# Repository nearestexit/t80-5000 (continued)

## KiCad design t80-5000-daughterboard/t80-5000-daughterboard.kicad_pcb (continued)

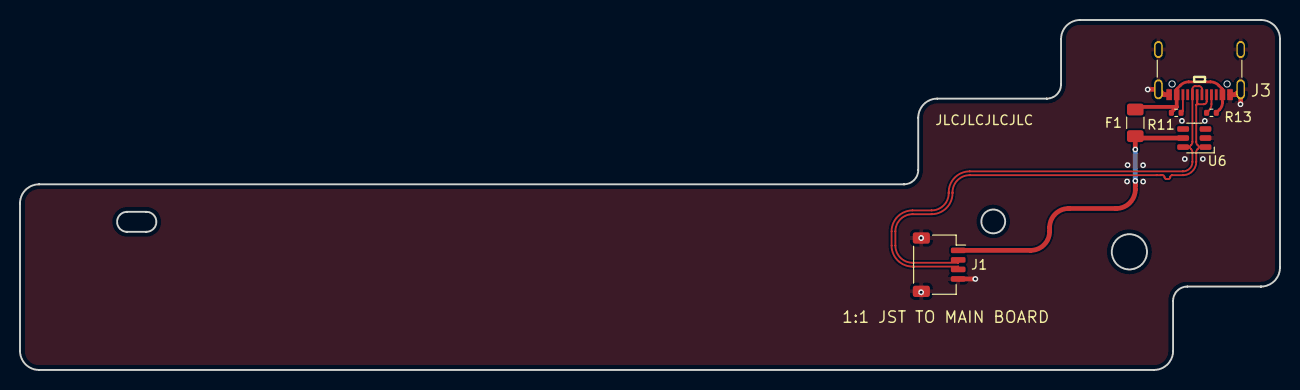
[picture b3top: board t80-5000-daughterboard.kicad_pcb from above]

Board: 2 copper layers, 132.3 x 36.8 mm, 6 parts (0 on the bottom side), 7 nets.

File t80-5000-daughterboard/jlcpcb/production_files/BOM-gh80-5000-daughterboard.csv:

Comment,Designator,Footprint,LCSC,Quantity
56k,"R11,R13",R_0402_1005Metric,C114756,2
Conn_01x04,J1,JST_SH_SM04B-SRSS-TB_1x04-1MP_P1.00mm_Horizontal,C371571,1
USB_C_Receptacle_USB2.0_16P,J3,USB-C-SMD_HANBO_MC-121-L119,C6332278,1
500mA,F1,Fuse_1206_3216Metric,C70076,1
SRV05-4,U6,SOT-23-6-routable,C85364,1

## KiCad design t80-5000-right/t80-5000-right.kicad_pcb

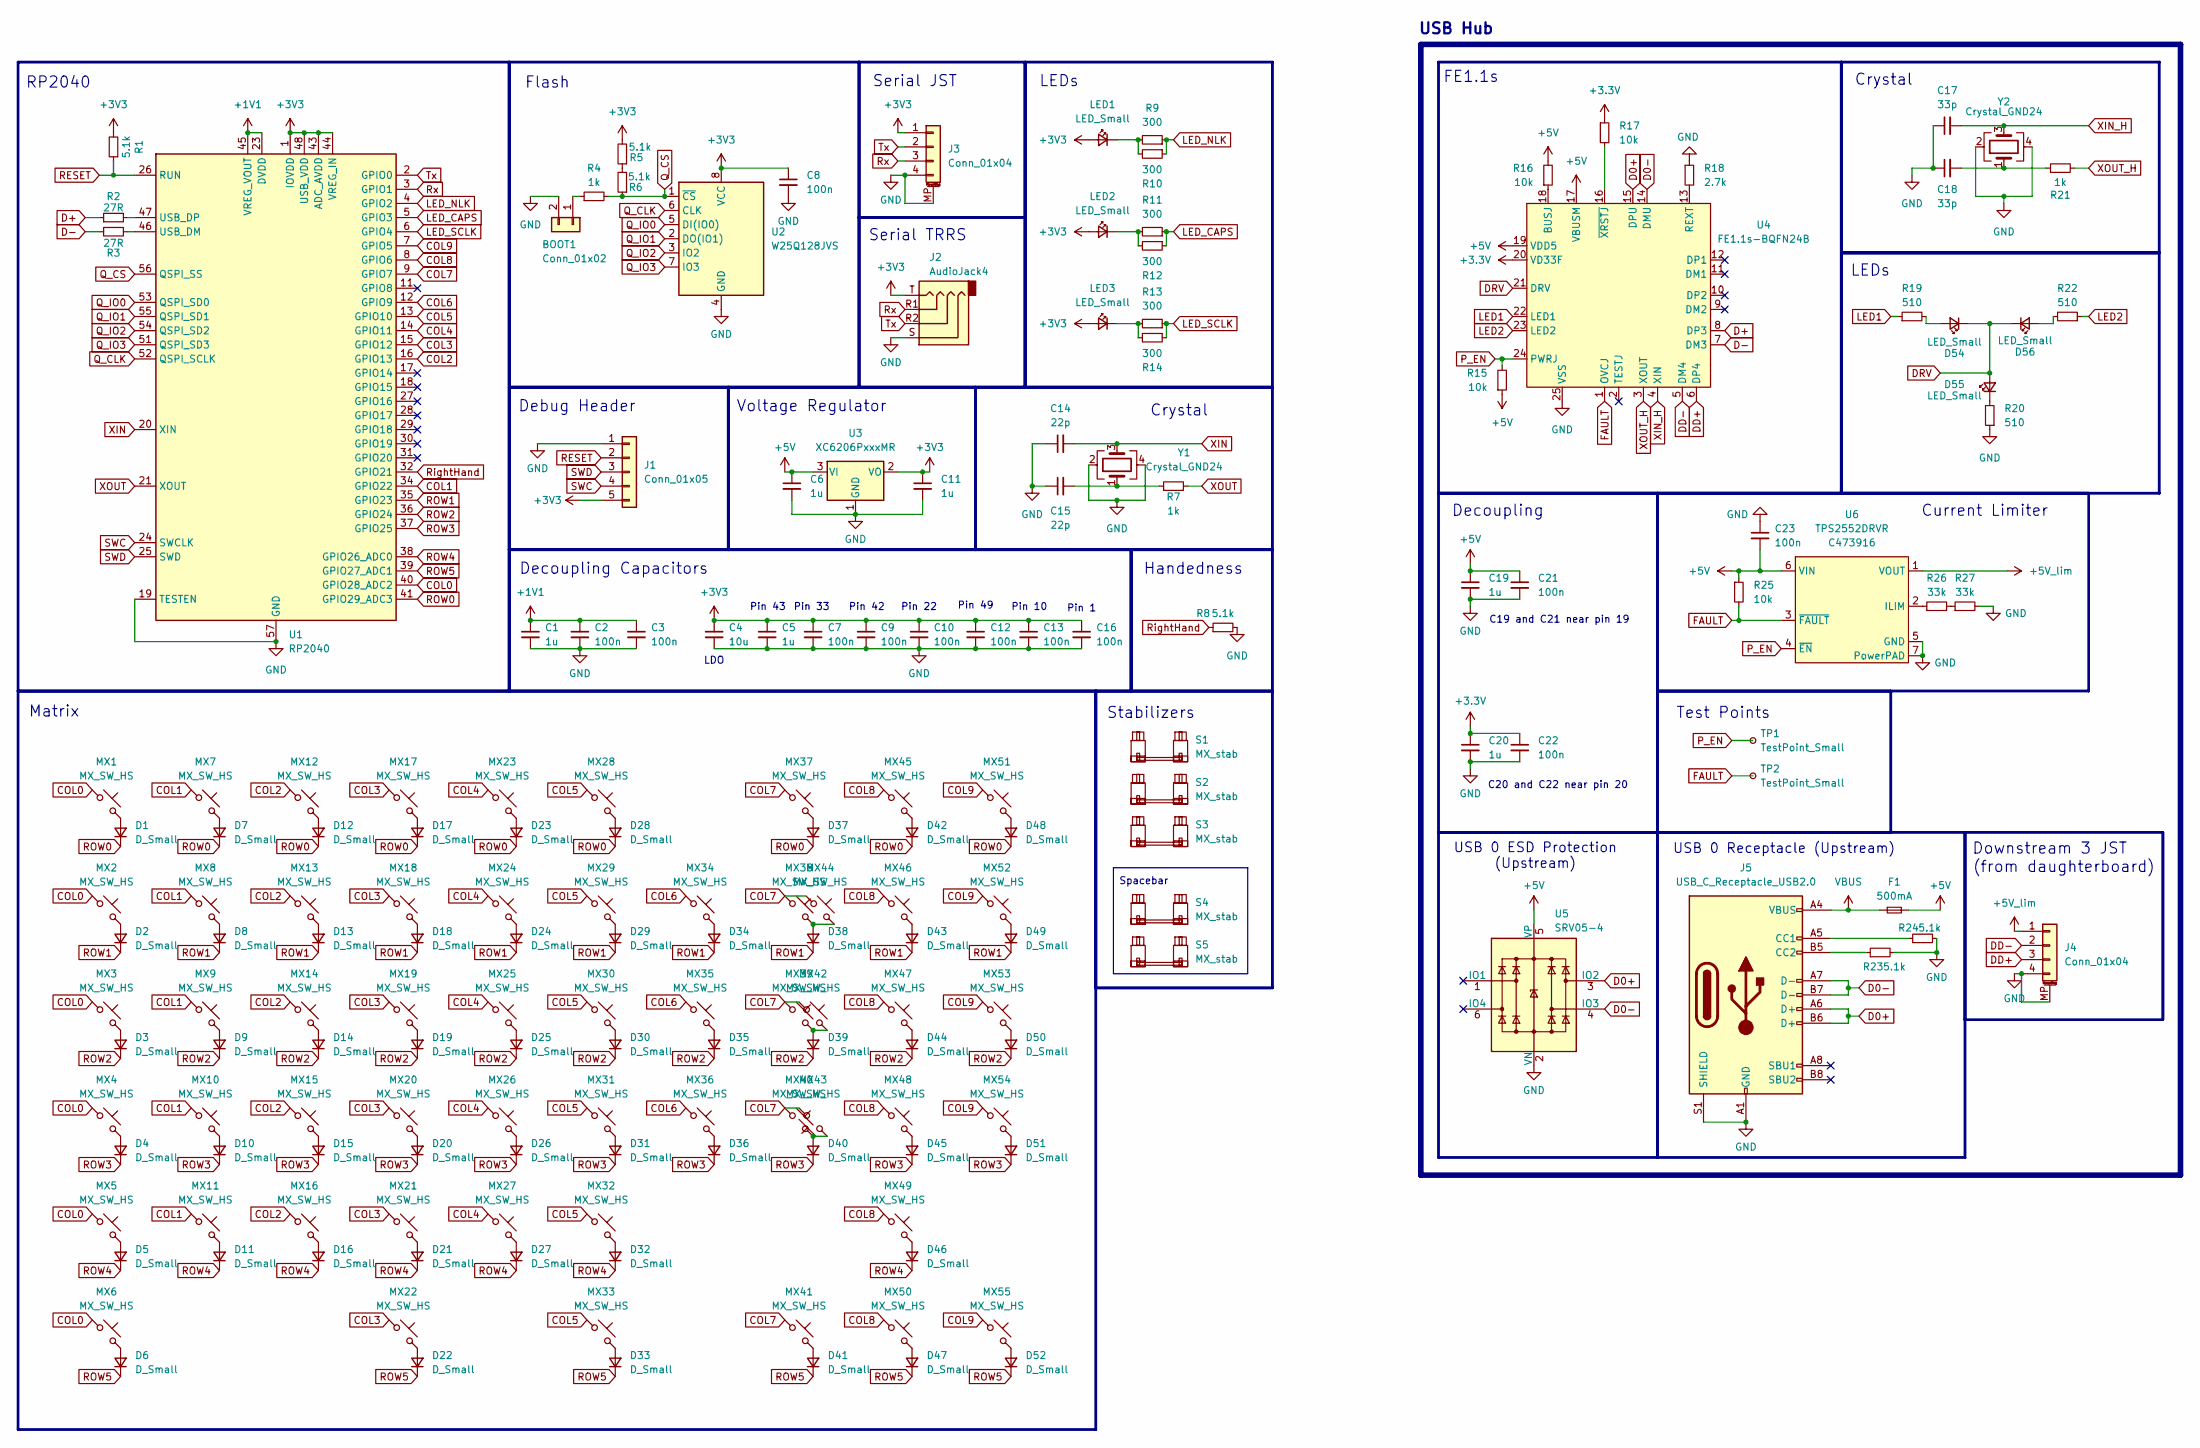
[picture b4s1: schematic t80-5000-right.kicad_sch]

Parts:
BOOT1: Conn_01x02; PinHeader_1x02_P2.54mm_Vertical
C1, C5, C6, C11, C19, C20: 1u; C_0402_1005Metric
C2, C3, C7, C8, C9, C10, C12, C13, C16, C21, C22, C23: 100n; C_0402_1005Metric
C4: 10u; C_0603_1608Metric
C14, C15: 22p; C_0402_1005Metric
C17, C18: 33p; C_0402_1005Metric
D1, D2, D3, D4, D5, D6, D7, D8, D9, D10, D11, D12, D13, D14, D15, D16, D17, D18, D19, D20, D21, D22, D23, D24, D25, D26, D27, D28, D29, D30, D31, D32, D33, D34, D35, D36, D37, D38, D39, D40, D41, D42, D43, D44, D45, D46, D47, D48, D49, D50, D51, D52: D_Small; D_SOD-123-ShiftedSoldermask
D54, D55, D56: LED_Small; LED_0603_1608Metric
F1: 500mA; Fuse_1206_3216Metric
J1: Conn_01x05; PinHeader_1x05_P2.54mm_Vertical
J2: AudioJack4; AUDIO-TH_XKB_PJ-320A
J3, J4: Conn_01x04; JST_SH_SM04B-SRSS-TB_1x04-1MP_P1.00mm_Horizontal
J5: USB_C_Receptacle_USB2.0; USB-C-SMD_GT-USB-7014D
LED1, LED2, LED3: LED_Small; LED_D5.0mm
MX1, MX2, MX3, MX4, MX5, MX6, MX7, MX8, MX9, MX10, MX11, MX12, MX13, MX14, MX15, MX16, MX17, MX18, MX19, MX20, MX21, MX22, MX23, MX24, MX25, MX26, MX27, MX28, MX29, MX30, MX31, MX32, MX33, MX34, MX35, MX36, MX37, MX38, MX39, MX40, MX41, MX42, MX43, MX44, MX45, MX46, MX47, MX48, MX49, MX50, MX51, MX52, MX53, MX54, MX55: MX_SW_HS; SW_MX_1u
R1, R5, R6, R23, R24: 5.1k; R_0402_1005Metric
R2, R3: 27R; R_0402_1005Metric
R4, R7, R21: 1k; R_0402_1005Metric
R8: 5.1k; R_0603_1608Metric_Pad0.98x0.95mm_HandSolder
R9, R11, R13: 300; R_Axial_DIN0207_L6.3mm_D2.5mm_P10.16mm_Horizontal
R10, R12, R14: 300; R_1206_3216Metric_Pad1.30x1.75mm_HandSolder
R15, R16, R17, R25: 10k; R_0402_1005Metric
R18: 2.7k; R_0603_1608Metric
R19, R20, R22: 510; R_0402_1005Metric
R26, R27: 33k; R_0402_1005Metric
S1, S2, S3: MX_stab; STAB_MX_P_2u
S4: MX_stab; STAB_MX_3.5u_5000
S5: MX_stab; STAB_MX_5000
TP1, TP2: TestPoint_Small; TestPoint_THTPad_D1.0mm_Drill0.5mm
U1: RP2040; QFN-56-1EP_7x7mm_P0.4mm_EP3.2x3.2mm
U2: W25Q128JVS; SOIC-8_5.23x5.23mm_P1.27mm
U3: XC6206PxxxMR; SOT-23-3
U4: FE1.1s-BQFN24B; WQFN-24-1EP_4x4mm_P0.5mm_EP2.6x2.6mm
U5: SRV05-4; SOT-23-6-routable
U6: TPS2552DRVR; WSON-6-1EP_2x2mm_P0.65mm_EP1x1.6mm_ThermalVias; LCSC C473916
Y1, Y2: Crystal_GND24; Crystal_SMD_3225-4Pin_3.2x2.5mm

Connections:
+1V1: C1.1, C2.1, C3.1, U1.23 (DVDD), U1.45 (VREG_VOUT), U1.50 (DVDD)
+3.3V: C20.1, C22.1, R17.1, U4.20 (VD33F)
+3V3: C4.1, C5.1, C7.1, C8.1, C9.1, C10.1, C11.1, C12.1, C13.1, C16.1, J1.5, J2.T, J3.1, LED1.2 (A), LED2.2 (A), LED3.2 (A), R1.2, R5.2, U1.1 (IOVDD), U1.10 (IOVDD), U1.22 (IOVDD), U1.33 (IOVDD), U1.42 (IOVDD), U1.43 (ADC_AVDD), U1.44 (VREG_IN), U1.48 (USB_VDD), U1.49 (IOVDD), U2.8 (VCC), U3.2 (VO)
+5V: C6.1, C19.1, C21.1, C23.2, F1.2, R15.1, R16.2, R25.1, U3.3 (VI), U4.17 (VBUSM), U4.19 (VDD5), U5.5 (VP), U6.6 (VIN)
+5V_lim: J4.1, U6.1 (VOUT)
COL0: MX1.1, MX2.1, MX3.1, MX4.1, MX5.1, MX6.1, U1.40 (GPIO28_ADC2)
COL1: MX7.1, MX8.1, MX9.1, MX10.1, MX11.1, U1.34 (GPIO22)
COL2: MX12.1, MX13.1, MX14.1, MX15.1, MX16.1, U1.16 (GPIO13)
COL3: MX17.1, MX18.1, MX19.1, MX20.1, MX21.1, MX22.1, U1.15 (GPIO12)
COL4: MX23.1, MX24.1, MX25.1, MX26.1, MX27.1, U1.14 (GPIO11)
COL5: MX28.1, MX29.1, MX30.1, MX31.1, MX32.1, MX33.1, U1.13 (GPIO10)
COL6: MX34.1, MX35.1, MX36.1, U1.12 (GPIO9)
COL7: MX37.1, MX38.1, MX39.1, MX40.1, MX41.1, MX42.1, MX43.2, MX44.1, U1.9 (GPIO7)
COL8: MX45.1, MX46.1, MX47.1, MX48.1, MX49.1, MX50.1, U1.8 (GPIO6)
COL9: MX51.1, MX52.1, MX53.1, MX54.1, MX55.1, U1.7 (GPIO5)
D0+: J5.A6 (D+), J5.B6 (D+), U4.15 (DPU), U5.3 (IO2)
D0-: J5.A7 (D-), J5.B7 (D-), U4.14 (DMU), U5.4 (IO3)
D+: R2.1, U4.8 (DP3)
D-: R3.2, U4.7 (DM3)
DD+: J4.3, U4.6 (DP4)
DD-: J4.2, U4.5 (DM4)
DRV: D54.1 (K), D55.2 (A), D56.1 (K), U4.21 (DRV)
FAULT: R25.2, TP2.1, U4.1 (OVCJ), U6.3 (~FAULT)
GND: BOOT1.2, C1.2, C2.2, C3.2, C4.2, C5.2, C6.2, C7.2, C8.2, C9.2, C10.2, C11.2, C12.2, C13.2, C14.1, C15.1, C16.2, C17.1, C18.1, C19.2, C20.2, C21.2, C22.2, C23.1, J1.1, J2.S, J3.4, J3.MP (MountPin), J4.4, J4.MP (MountPin), J5.A1 (GND), J5.A12 (GND), J5.B1 (GND), J5.B12 (GND), J5.S1 (SHIELD), R8.2, R18.1, R20.1, R23.2, R24.2, R27.2, U1.19 (TESTEN), U1.57 (GND), U2.4 (GND), U3.1 (GND), U4.25 (VSS), U5.2 (VN), U6.5 (GND), U6.7 (PowerPAD), Y1.2, Y1.4, Y2.2, Y2.4
LED1: R19.1, U4.22 (LED1)
LED2: R22.1, U4.23 (LED2)
LED_CAPS: R11.1, R12.1, U1.5 (GPIO3)
LED_NLK: R9.1, R10.1, U1.4 (GPIO2)
LED_SCLK: R13.1, R14.1, U1.6 (GPIO4)
unnamed: BOOT1.1, R4.1
unnamed: C15.2, R7.1, Y1.1
unnamed: C18.2, R21.1, Y2.1
unnamed: D1.2 (A), MX1.2
unnamed: D2.2 (A), MX2.2
unnamed: D3.2 (A), MX3.2
unnamed: D4.2 (A), MX4.2
unnamed: D5.2 (A), MX5.2
unnamed: D6.2 (A), MX6.2
unnamed: D7.2 (A), MX7.2
unnamed: D8.2 (A), MX8.2
unnamed: D9.2 (A), MX9.2
unnamed: D10.2 (A), MX10.2
unnamed: D11.2 (A), MX11.2
unnamed: D12.2 (A), MX12.2
unnamed: D13.2 (A), MX13.2
unnamed: D14.2 (A), MX14.2
unnamed: D15.2 (A), MX15.2
unnamed: D16.2 (A), MX16.2
unnamed: D17.2 (A), MX17.2
unnamed: D18.2 (A), MX18.2
unnamed: D19.2 (A), MX19.2
unnamed: D20.2 (A), MX20.2
unnamed: D21.2 (A), MX21.2
unnamed: D22.2 (A), MX22.2
unnamed: D23.2 (A), MX23.2
unnamed: D24.2 (A), MX24.2
unnamed: D25.2 (A), MX25.2
unnamed: D26.2 (A), MX26.2
unnamed: D27.2 (A), MX27.2
unnamed: D28.2 (A), MX28.2
unnamed: D29.2 (A), MX29.2
unnamed: D30.2 (A), MX30.2
unnamed: D31.2 (A), MX31.2
unnamed: D32.2 (A), MX32.2
unnamed: D33.2 (A), MX33.2
unnamed: D34.2 (A), MX34.2
unnamed: D35.2 (A), MX35.2
unnamed: D36.2 (A), MX36.2
unnamed: D37.2 (A), MX37.2
unnamed: D38.2 (A), MX38.2, MX44.2
unnamed: D39.2 (A), MX39.2, MX42.2
unnamed: D40.2 (A), MX40.2, MX43.1
unnamed: D41.2 (A), MX41.2
unnamed: D42.2 (A), MX45.2
unnamed: D43.2 (A), MX46.2
unnamed: D44.2 (A), MX47.2
unnamed: D45.2 (A), MX48.2
unnamed: D46.2 (A), MX49.2
unnamed: D47.2 (A), MX50.2
unnamed: D48.2 (A), MX51.2
unnamed: D49.2 (A), MX52.2
unnamed: D50.2 (A), MX53.2
unnamed: D51.2 (A), MX54.2
unnamed: D52.2 (A), MX55.2
unnamed: D54.2 (A), R19.2
unnamed: D55.1 (K), R20.2
unnamed: D56.2 (A), R22.2
unnamed: J5.A5 (CC1), R24.1
unnamed: J5.B5 (CC2), R23.1
unnamed: LED1.1 (K), R9.2, R10.2
unnamed: LED2.1 (K), R11.2, R12.2
unnamed: LED3.1 (K), R13.2, R14.2
unnamed: R5.1, R6.2
unnamed: R26.2, R27.1
unnamed: R3.1, U1.46 (USB_DM)
unnamed: R2.2, U1.47 (USB_DP)
unnamed: R16.1, U4.18 (BUSJ)
unnamed: R18.2, U4.13 (REXT)
unnamed: R17.2, U4.16 (~XRSTJ)
unnamed: R26.1, U6.2 (ILIM)
P_EN: R15.2, TP1.1, U4.24 (PWRJ), U6.4 (~EN)
Q_CLK: U1.52 (QSPI_SCLK), U2.6 (CLK)
Q_CS: R4.2, R6.1, U1.56 (QSPI_SS), U2.1 (~CS)
Q_IO0: U1.53 (QSPI_SD0), U2.5 (DI(IO0))
Q_IO1: U1.55 (QSPI_SD1), U2.2 (DO(IO1))
Q_IO2: U1.54 (QSPI_SD2), U2.3 (IO2)
Q_IO3: U1.51 (QSPI_SD3), U2.7 (IO3)
RESET: J1.2, R1.1, U1.26 (RUN)
ROW0: D1.1 (K), D7.1 (K), D12.1 (K), D17.1 (K), D23.1 (K), D28.1 (K), D37.1 (K), D42.1 (K), D48.1 (K), U1.41 (GPIO29_ADC3)
ROW1: D2.1 (K), D8.1 (K), D13.1 (K), D18.1 (K), D24.1 (K), D29.1 (K), D34.1 (K), D38.1 (K), D43.1 (K), D49.1 (K), U1.35 (GPIO23)
ROW2: D3.1 (K), D9.1 (K), D14.1 (K), D19.1 (K), D25.1 (K), D30.1 (K), D35.1 (K), D39.1 (K), D44.1 (K), D50.1 (K), U1.36 (GPIO24)
ROW3: D4.1 (K), D10.1 (K), D15.1 (K), D20.1 (K), D26.1 (K), D31.1 (K), D36.1 (K), D40.1 (K), D45.1 (K), D51.1 (K), U1.37 (GPIO25)
ROW4: D5.1 (K), D11.1 (K), D16.1 (K), D21.1 (K), D27.1 (K), D32.1 (K), D46.1 (K), U1.38 (GPIO26_ADC0)
ROW5: D6.1 (K), D22.1 (K), D33.1 (K), D41.1 (K), D47.1 (K), D52.1 (K), U1.39 (GPIO27_ADC1)
RightHand: R8.1, U1.32 (GPIO21)
Rx: J2.R1, J3.3, U1.3 (GPIO1)
SWC: J1.4, U1.24 (SWCLK)
SWD: J1.3, U1.25 (SWD)
Tx: J2.R2, J3.2, U1.2 (GPIO0)
VBUS: F1.1, J5.A4 (VBUS), J5.A9 (VBUS), J5.B4 (VBUS), J5.B9 (VBUS)
XIN: C14.2, U1.20 (XIN), Y1.3
XIN_H: C17.2, U4.4 (XIN), Y2.3
XOUT: R7.2, U1.21 (XOUT)
XOUT_H: R21.2, U4.3 (XOUT)

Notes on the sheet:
Decoupling
Serial TRRS
Pin 10
LDO
Spacebar
Decoupling Capacitors
Serial JST
Crystal
FE1.1s
LEDs
Pin 43
Downstream 3 JST
Pin 42
USB Hub
Stabilizers
USB 0 Receptacle (Upstream)
(from daughterboard)
Debug Header
C19 and C21 near pin 19
Pin 22
C20 and C22 near pin 20
Test Points
Current Limiter
Pin 33
USB 0 ESD Protection (Upstream)
Pin 49
RP2040
Matrix
Handedness
Flash
Pin 1
Voltage Regulator

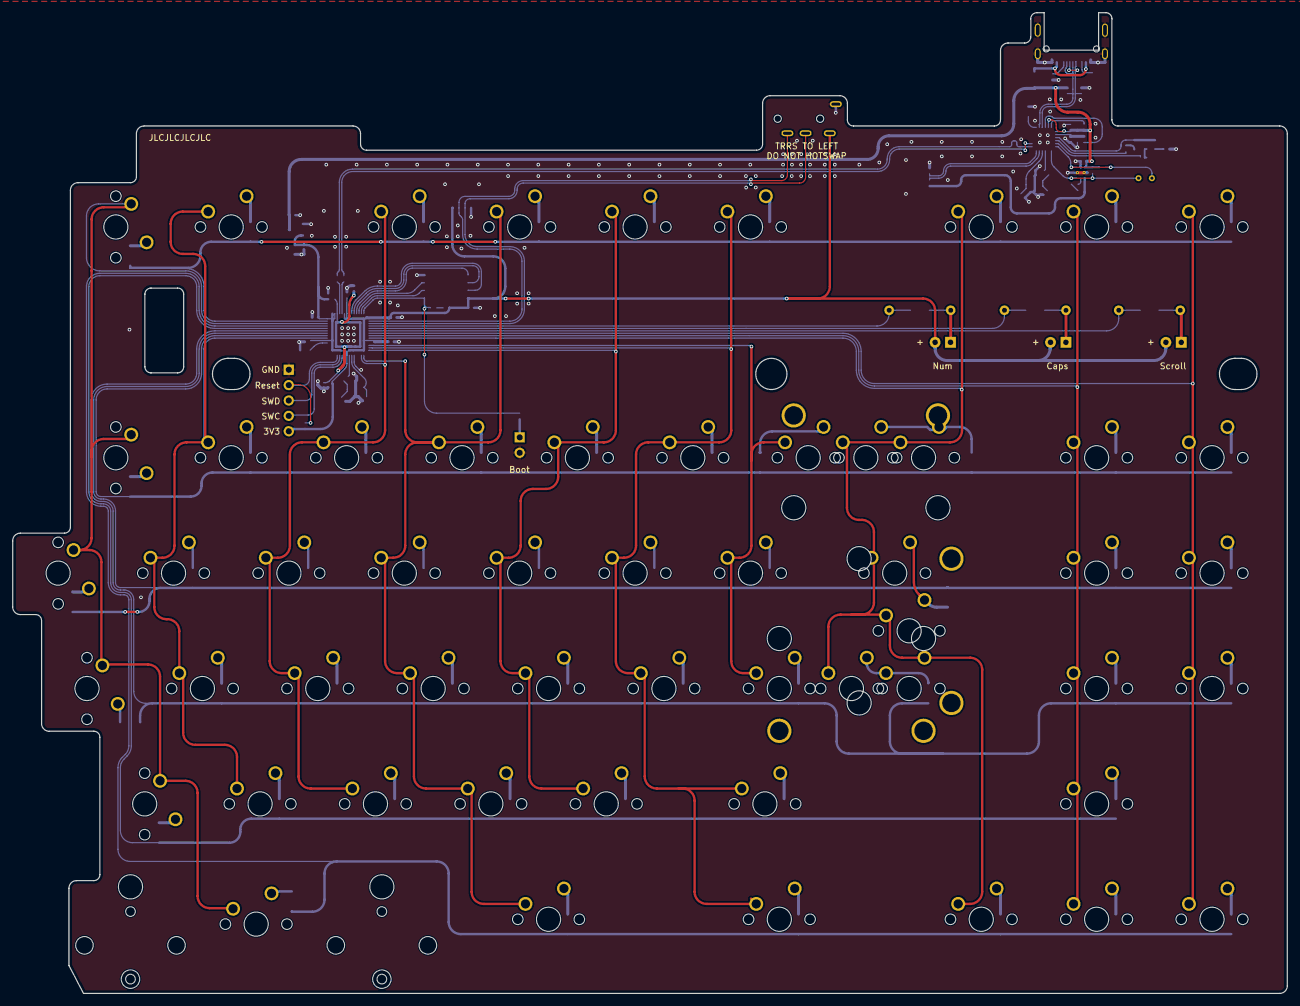
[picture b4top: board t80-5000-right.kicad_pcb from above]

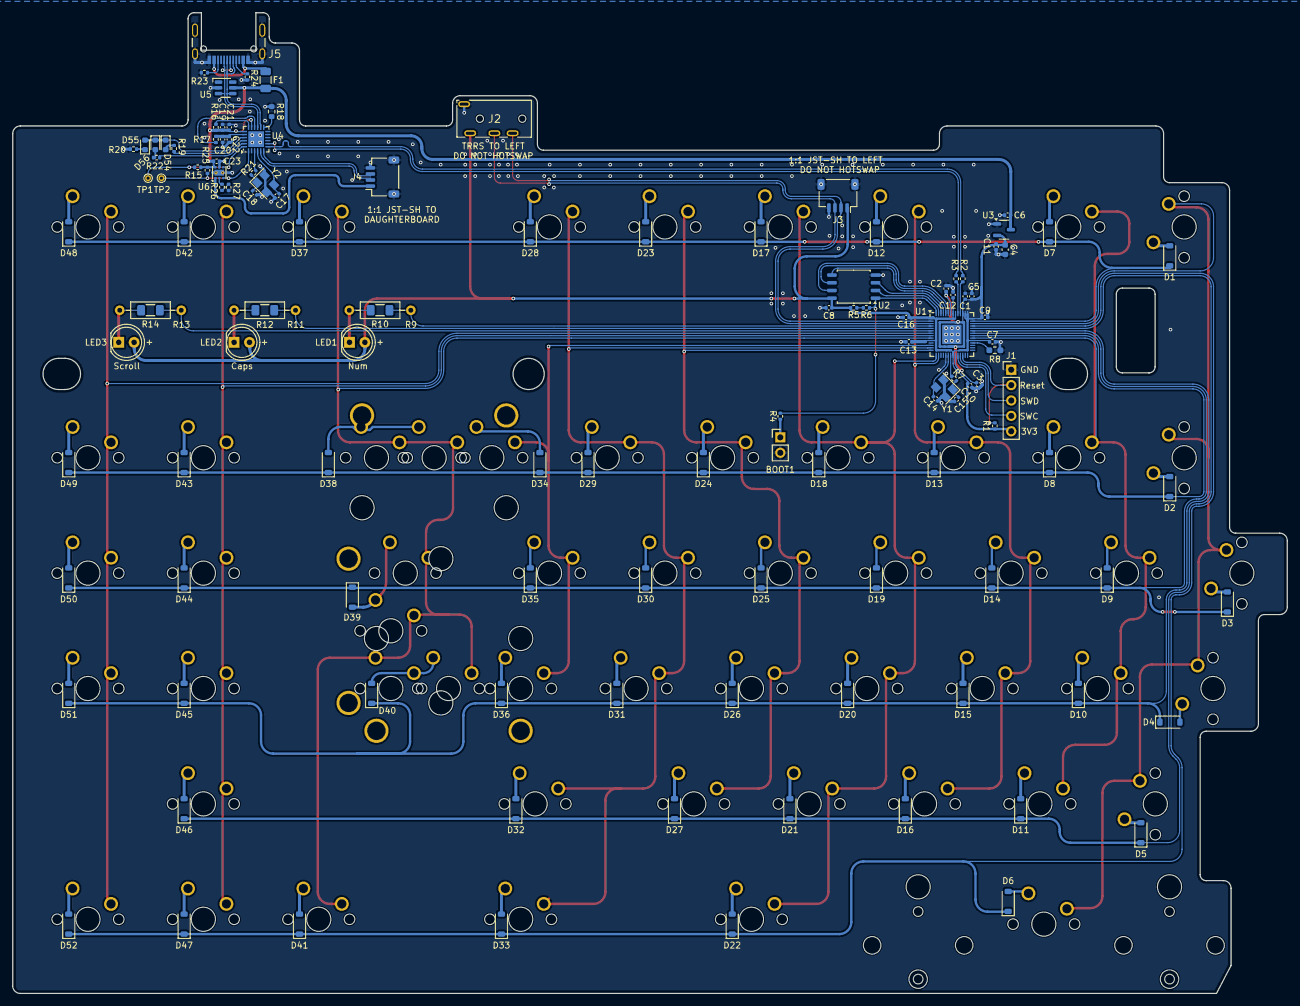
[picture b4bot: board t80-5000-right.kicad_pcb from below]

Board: 2 copper layers, 210.4 x 161.9 mm, 185 parts (125 on the bottom side), 124 nets.

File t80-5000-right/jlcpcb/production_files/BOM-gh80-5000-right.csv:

Comment,Designator,Footprint,LCSC,Quantity
1k,"R21,R4,R7",R_0402_1005Metric,C11702,3
W25Q128JVS,U2,SOIC-8_5.23x5.23mm_P1.27mm,C131025,1
2.7k,R18,R_0603_1608Metric,C13167,1
27R,"R2,R3",R_0402_1005Metric,C138021,2
22p,"C14,C15",C_0402_1005Metric,C1555,2
33p,"C17,C18",C_0402_1005Metric,C1562,2
300,"R10,R12,R14",R_1206_3216Metric_Pad1.30x1.75mm_HandSolder,C17887,3
10u,C4,C_0603_1608Metric,C19702,1
RP2040,U1,QFN-56-1EP_7x7mm_P0.4mm_EP3.2x3.2mm,C2040,1
LED_Small,"D54,D55,D56",LED_0603_1608Metric,C2290,3
5.1k,R8,R_0603_1608Metric_Pad0.98x0.95mm_HandSolder,C23186,1
510,"R19,R20,R22",R_0402_1005Metric,C25123,3
10k,"R15,R16,R17,R25",R_0402_1005Metric,C25744,4
33k,"R26,R27",R_0402_1005Metric,C25779,2
5.1k,"R1,R23,R24,R5,R6",R_0402_1005Metric,C25905,5
AudioJack4,J2,AUDIO-TH_XKB_PJ-320A,C2884926,1
USB_C_Receptacle_USB2.0,J5,USB-C-SMD_GT-USB-9014AB,C3019720,1
100n,"C10,C12,C13,C16,C2,C21,C22,C23,C3,C7,C8,C9",C_0402_1005Metric,C307331,12
Conn_01x04,"J3,J4",JST_SH_SM04B-SRSS-TB_1x04-1MP_P1.00mm_Horizontal,C371571,2
TPS2552DRVR,U6,WSON-6-1EP_2x2mm_P0.65mm_EP1x1.6mm_ThermalVias,C473916,1
1u,"C1,C11,C19,C20,C5,C6",C_0402_1005Metric,C52923,6
XC6206PxxxMR,U3,SOT-23-3,C5446,1
FE1.1s-BQFN24B,U4,WQFN-24-1EP_4x4mm_P0.5mm_EP2.6x2.6mm,C6776948,1
500mA,F1,Fuse_1206_3216Metric,C70076,1
D_Small,"D1,D10,D11,D12,D13,D14,D15,D16,D17,D18,D19,D2,D20,D21,D22,D23,D24,D25,D26,D27,D28,D29,D3,D30,D31,D32,D33,D34,D35,D36,D37,D38,D39,D4,D40,D41,D42,D43,D44,D45,D46,D47,D48,D49,D5,D50,D51,D52,D6,D7,D8,D9",D_SOD-123-ShiftedSoldermask,C81598,52
SRV05-4,U5,SOT-23-6-routable,C85364,1
Crystal_GND24,"Y1,Y2",Crystal_SMD_3225-4Pin_3.2x2.5mm,C9002,2

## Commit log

2024-12-15 add firmware
2024-12-15 Update README.md with firmware instructions
2025-04-28 fix noncritical missing trace on 5700
2025-04-29 Fix dead link
